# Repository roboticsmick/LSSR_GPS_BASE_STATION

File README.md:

# LSSR_GPS_BASE_STATION

A portable, low cost GPS Rocket tracking base station. Uses a Teensy 4.1 and Ebytes LORA module to track and display the current GPS coordinates for a HPR rocket launch. Estimated range is 7km.

This was designed and built for my HPR L1 certification launch. Tracking worked perfectly and I was able to successfully monitor the launch of my rocket, then use the GPS coordinates to locate it’s landing point.

Parts list:
* Microcontroller – TEENSY 4.1
* RF receiver – EbyteLORA E22-900T22D (set to 915Mhz for Australia)
* GPS – UBLOX NEO_6M (also works with ATGM336H GPS Module)
* 5V Buck Converter – MPM3610 5V at 1.2A
* Compass – GY271 QMC5883 LCD – OLED 128×64
* Battery – 7.4V LIPO with XT30 connection

Version 2 will use a Raspberry Pi Pico RP2040 to bring the overall costs of the board down.

PCB design was done using Fusion 360 electronics. 

PCB printed using JLCPCB.

Case design is lasercut perspex and 3D printed. Modelled using Fusion 360.

Instructions:
When recording GPS coodinates for launch data. 
1. Power using a USB only (do not turn on the toggle switch).
2. Connect to PC using USB. 
3. Use the device manager to identify which COM port the GPS Base Station is connected to.

4. Open putty (don't use the serial monitor in Arduino as it does not allow saving data and has a limited number of rows).
5. Set to serial and change the COM port to match the ID found in the device manager.

6. Base stations should automaticaly pick up the GPS tracker when turned on.
7. The base station will start displaying GPS coordinates on the LCD when it has a fix.
8. SIV = Satellites in view. At least 3 should be in view to get valid data. 
9. When the rocket has landed, save the GPS coordinate data from putty as a CSV. 
10. Copy the last row of the saved data and paste it into Googlemaps. The rocket coordinates should now be available.

If the rocket coordinates were lost:
1. Unplug the USB, and turn on the GPS base station using the toggle switch.
2. Head in the direction of the last known coordinates.
3. When new coordinates are recieved by the base station, the GPS base station should update on the LCD when the rocket is detected. 
4. If you cannot see the rocket, enter the updated coordinates into your phones googlemaps, and you should be able to work out the location in the field.

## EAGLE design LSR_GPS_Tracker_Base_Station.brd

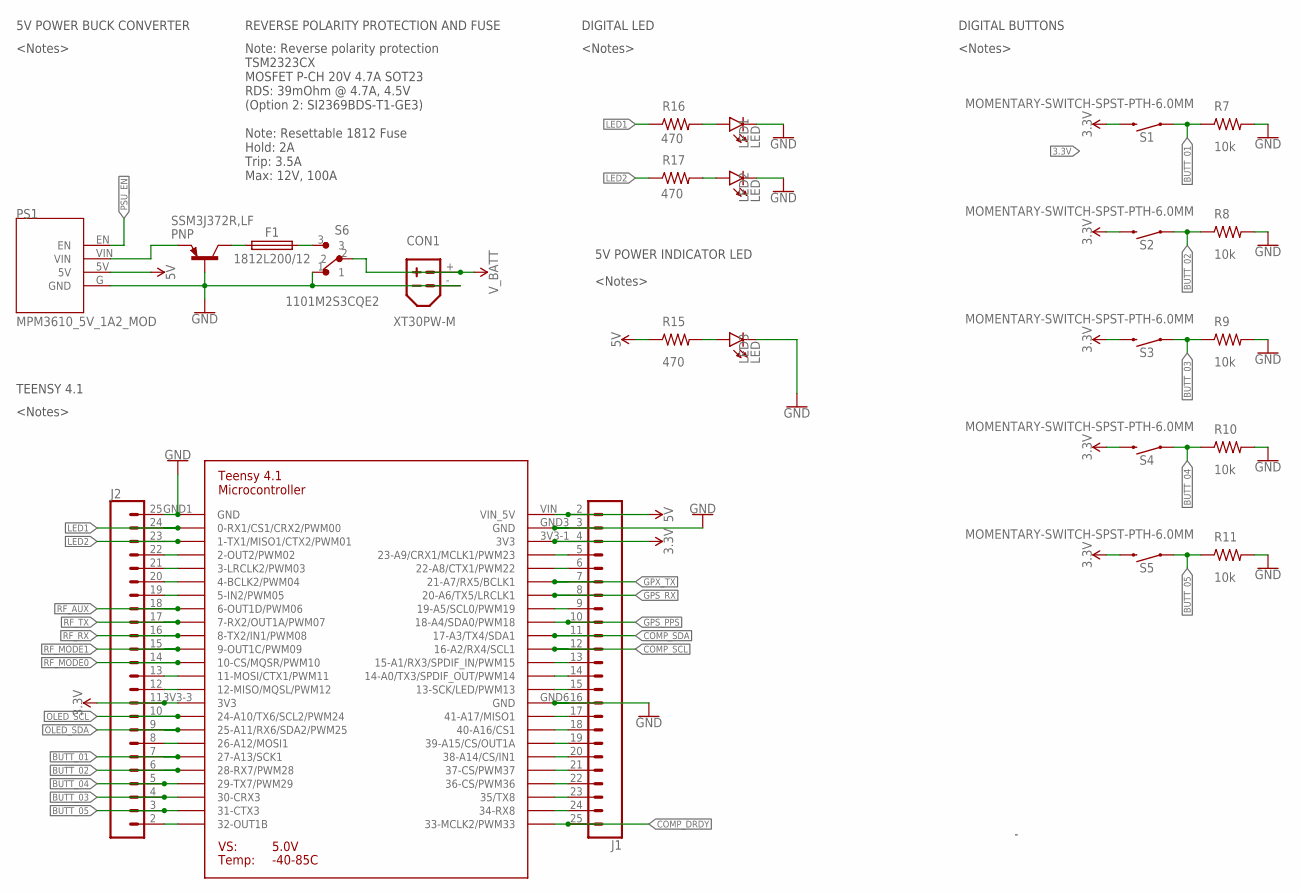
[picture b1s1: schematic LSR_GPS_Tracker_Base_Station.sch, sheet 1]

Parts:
CON1: XT30PW-M; XT30PW-PLUG
F1: 1812L200/12; FUSC4532X125
J1, J2: CONN_24; 1X24
LED1, LED2, LED3: LED; 0805_LED
PS1: MPM3610_5V_1A2_MOD; MPM3610_5V_1A2_FP
R7, R8, R9, R10, R11: 10k; 0805_RESISTOR_FP
R15, R16, R17: 470; 0805_RESISTOR_FP
S1, S2, S3, S4, S5: MOMENTARY-SWITCH-SPST-PTH-6.0MM; TACTILE_SWITCH_PTH_6.0MM
S6: 1101M2S3CQE2; SW_1101M2S3CQE2
SSM3J372R,LF: PNP; SOT95P237X112-3N
U$3: TEENSY_4_1; TEENSY_4_1_FP

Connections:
3.3V: J1.4, J2.11, S1.3 (2), S2.3 (2), S3.3 (2), S4.3 (2), S5.3 (2), U$3.3V3-1 (3V3), U$3.3V3-3 (3V3); also elsewhere on the board
5V: J1.2, PS1.5V, R15.1, U$3.VIN (VIN_5V); also elsewhere on the board
BUTT_01: J2.7, R7.1, S1.1, U$3.27-A13/SCK1
BUTT_02: J2.6, R8.1, S2.1, U$3.28-RX7/PWM28
BUTT_03: J2.4, R9.1, S3.1, U$3.30-CRX3
BUTT_04: J2.5, R10.1, S4.1, U$3.29-TX7/PWM29
BUTT_05: J2.3, R11.1, S5.1, U$3.31-CTX3
COMP_DRDY: J1.25, U$3.33-MCLK2/PWM33; also elsewhere on the board
COMP_SCL: J1.12, U$3.16-A2/RX4/SCL1; also elsewhere on the board
COMP_SDA: J1.11, U$3.17-A3/TX4/SDA1; also elsewhere on the board
GND: CON1.-, J1.3, J1.16, J2.25, LED1.C, LED2.C, LED3.C, PS1.G (GND), R7.2, R8.2, R9.2, R10.2, R11.2, S6.1, SSM3J372R,LF.1 (B), U$3.GND1 (GND), U$3.GND3 (GND), U$3.GND6 (GND); also elsewhere on the board
GPS_PPS: J1.10, U$3.18-A4/SDA0/PWM18; also elsewhere on the board
GPS_RX: J1.8, U$3.20-A6/TX5/LRCLK1; also elsewhere on the board
GPX_TX: J1.7, U$3.21-A7/RX5/BCLK1; also elsewhere on the board
LED1: J2.24, R16.1, U$3.0-RX1/CS1/CRX2/PWM00
LED2: J2.23, R17.1, U$3.1-TX1/MISO1/CTX2/PW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
unnamed: J1.5, U$3.23-A9/CRX1/MCLK1/PW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
unnamed: J1.6, U$3.22-A8/CTX1/PWM22
unnamed: J1.13, U$3.15-A1/RX3/SPDIF_IN/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
unnamed: J2.2, U$3.32-OUT1B
unnamed: J1.14, U$3.14-A0/TX3/SPDIF_OUT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
unnamed: J1.15, U$3.13-SCK/LED/PWM13
unnamed: J1.17, U$3.41-A17/MISO1
unnamed: J1.18, U$3.40-A16/CS1
unnamed: J1.19, U$3.39-A15/CS/OUT1A
unnamed: J1.20, U$3.38-A14/CS/IN1
unnamed: J1.21, U$3.37-CS/PWM37
unnamed: J1.22, U$3.36-CS/PWM36
unnamed: J1.23, U$3.35-TX8 (35/TX8)
unnamed: J1.24, U$3.34-RX8
unnamed: J1.9, U$3.19-A5/SCL0/PWM19
unnamed: J2.21, U$3.3-LRCLK2/PWM03
unnamed: J2.20, U$3.4-BCLK2/PWM04
unnamed: J2.19, U$3.5-IN2/PWM05
unnamed: J2.13, U$3.11-MOSI/CTX1/PWM11
unnamed: J2.12, U$3.12-MISO/MQSL/PWM12
unnamed: J2.8, U$3.26-A12/MOSI1
unnamed: J2.22, U$3.2-OUT2/PWM02
unnamed: LED3.A, R15.2
unnamed: LED1.A, R16.2
unnamed: F1.2, S6.3
unnamed: F1.1, SSM3J372R,LF.3 (C)
unnamed: PS1.VIN, SSM3J372R,LF.2 (E)
unnamed: LED2.A, R17.2
OLED_SCL: J2.10, U$3.24-A10/TX6/SCL2/PWM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; also elsewhere on the board
OLED_SDA: J2.9, U$3.25-A11/RX6/SDA2/PWM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; also elsewhere on the board
PSU_EN: PS1.EN
RF_AUX: J2.18, U$3.6-OUT1D/PWM06; also elsewhere on the board
RF_MODE0: J2.14, U$3.10-CS\MQSR/PWM10 (10-CS/MQSR/PWM10); also elsewhere on the board
RF_MODE1: J2.15, U$3.9-OUT1C/PWM09; also elsewhere on the board
RF_RX: J2.16, U$3.8-TX2/IN1/PWM08; also elsewhere on the board
RF_TX: J2.17, U$3.7-RX2/OUT1A/PWM07; also elsewhere on the board
V_BATT: CON1.+, S6.2

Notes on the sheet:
DIGITAL BUTTONS
5V POWER BUCK CONVERTER
DIGITAL LED
5V POWER INDICATOR LED
REVERSE POLARITY PROTECTION AND FUSE
TEENSY 4.1
<Notes>
Note: Reverse polarity protection TSM2323CX MOSFET P-CH 20V 4.7A SOT23 RDS: 39mOhm @ 4.7A, 4.5V (Option 2: SI2369BDS-T1-GE3) Note: Resettable 1812 Fuse Hold: 2A Trip: 3.5A Max: 12V, 100A

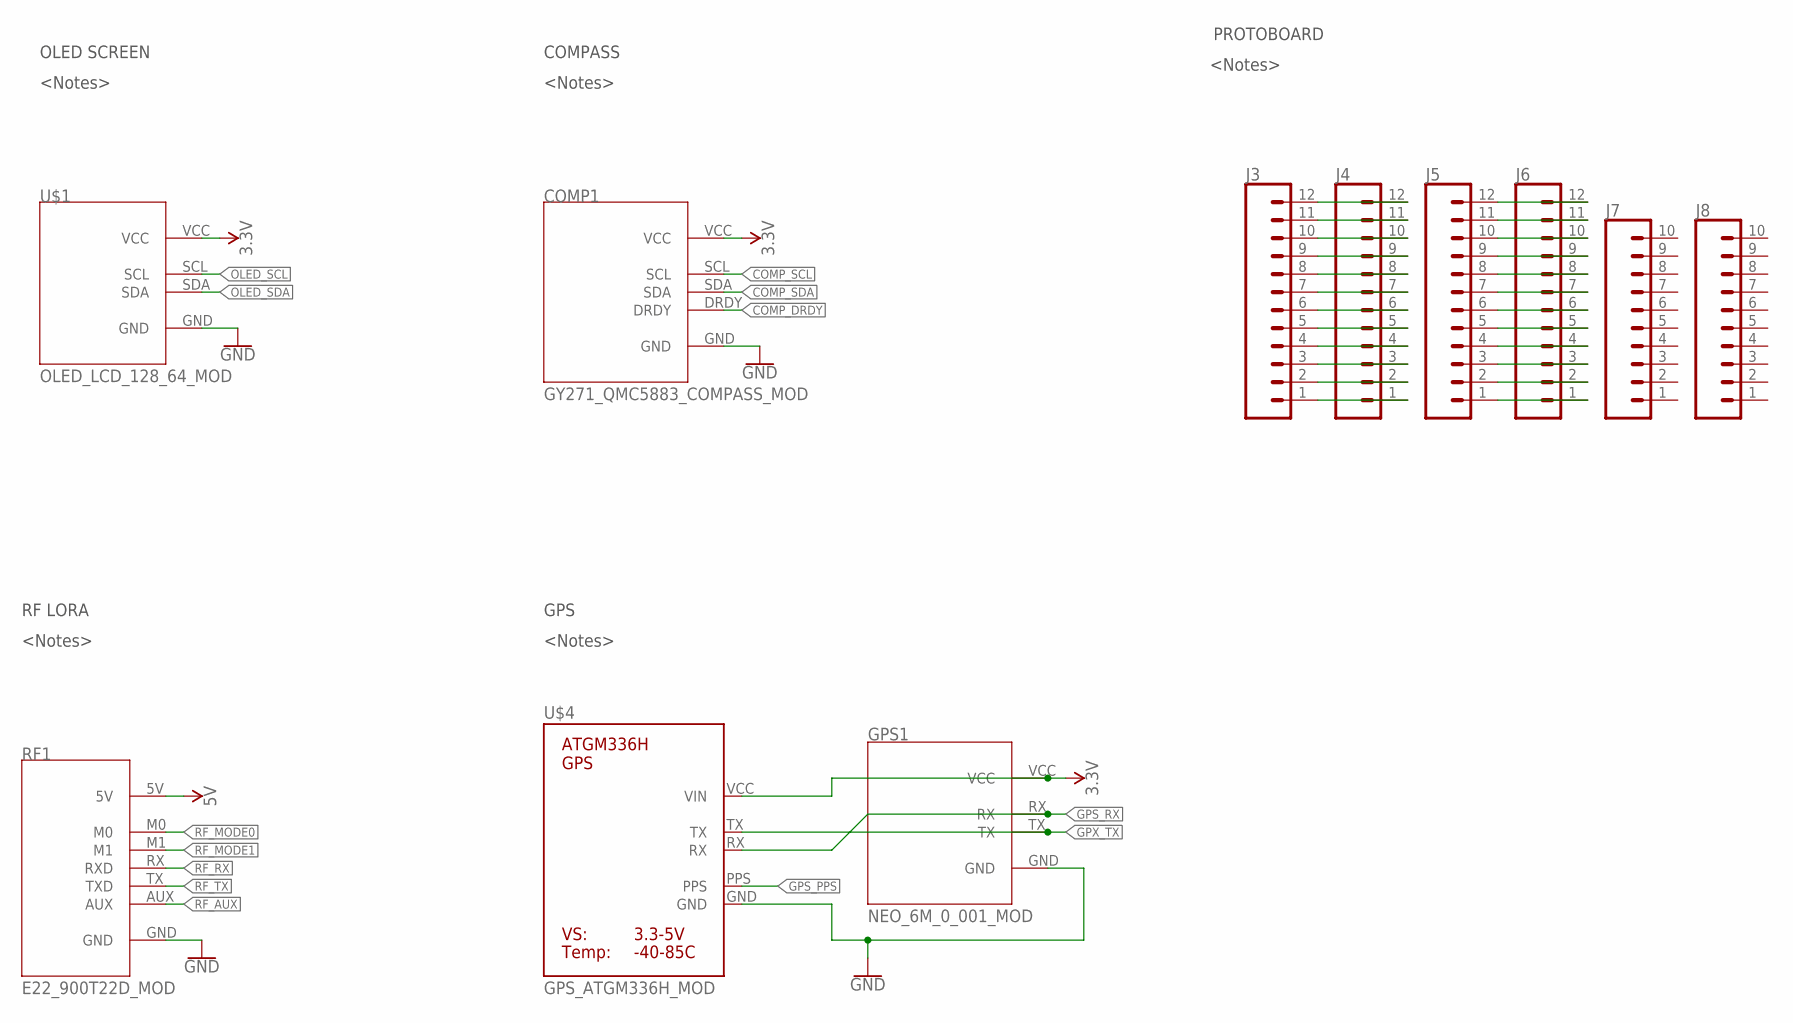
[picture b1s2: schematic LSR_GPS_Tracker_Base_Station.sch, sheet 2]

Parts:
COMP1: GY271_QMC5883_COMPASS_MOD; GY271_QMC5883_COMPASS_MOD_FP
GPS1: NEO_6M_0_001_MOD; NEO_6M_0_001_MOD_FP
J3, J4, J5, J6: CONN_12NO_SILK; 1X12_NO_SILK
J7, J8: CONN_10NO_SILK_PTH_FEMALE; 1X10_NO_SILK
RF1: E22_900T22D_MOD; E22_900T22D_MOD_FP
U$1: OLED_LCD_128_64_MOD; OLED_LCD_128_64_MOD_FP
U$4: GPS_ATGM336H_MOD; GPS_ATGM336H_FP

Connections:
3.3V: COMP1.VCC, GPS1.VCC, U$1.VCC, U$4.VCC (VIN); also elsewhere on the board
5V: RF1.5V; also elsewhere on the board
COMP_DRDY: COMP1.DRDY; also elsewhere on the board
COMP_SCL: COMP1.SCL; also elsewhere on the board
COMP_SDA: COMP1.SDA; also elsewhere on the board
GND: COMP1.GND, GPS1.GND, RF1.GND, U$1.GND, U$4.GND; also elsewhere on the board
GPS_PPS: U$4.PPS; also elsewhere on the board
GPS_RX: GPS1.RX, U$4.RX; also elsewhere on the board
GPX_TX: GPS1.TX, U$4.TX; also elsewhere on the board
unnamed: J3.12, J4.12
unnamed: J3.11, J4.11
unnamed: J3.10, J4.10
unnamed: J3.9, J4.9
unnamed: J3.8, J4.8
unnamed: J3.7, J4.7
unnamed: J3.6, J4.6
unnamed: J3.5, J4.5
unnamed: J3.4, J4.4
unnamed: J3.3, J4.3
unnamed: J3.2, J4.2
unnamed: J3.1, J4.1
unnamed: J5.12, J6.12
unnamed: J5.11, J6.11
unnamed: J5.10, J6.10
unnamed: J5.9, J6.9
unnamed: J5.8, J6.8
unnamed: J5.7, J6.7
unnamed: J5.6, J6.6
unnamed: J5.5, J6.5
unnamed: J5.4, J6.4
unnamed: J5.3, J6.3
unnamed: J5.2, J6.2
unnamed: J5.1, J6.1
OLED_SCL: U$1.SCL; also elsewhere on the board
OLED_SDA: U$1.SDA; also elsewhere on the board
RF_AUX: RF1.AUX; also elsewhere on the board
RF_MODE0: RF1.M0; also elsewhere on the board
RF_MODE1: RF1.M1; also elsewhere on the board
RF_RX: RF1.RX (RXD); also elsewhere on the board
RF_TX: RF1.TX (TXD); also elsewhere on the board

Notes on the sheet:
PROTOBOARD
GPS
RF LORA
COMPASS
OLED SCREEN
<Notes>

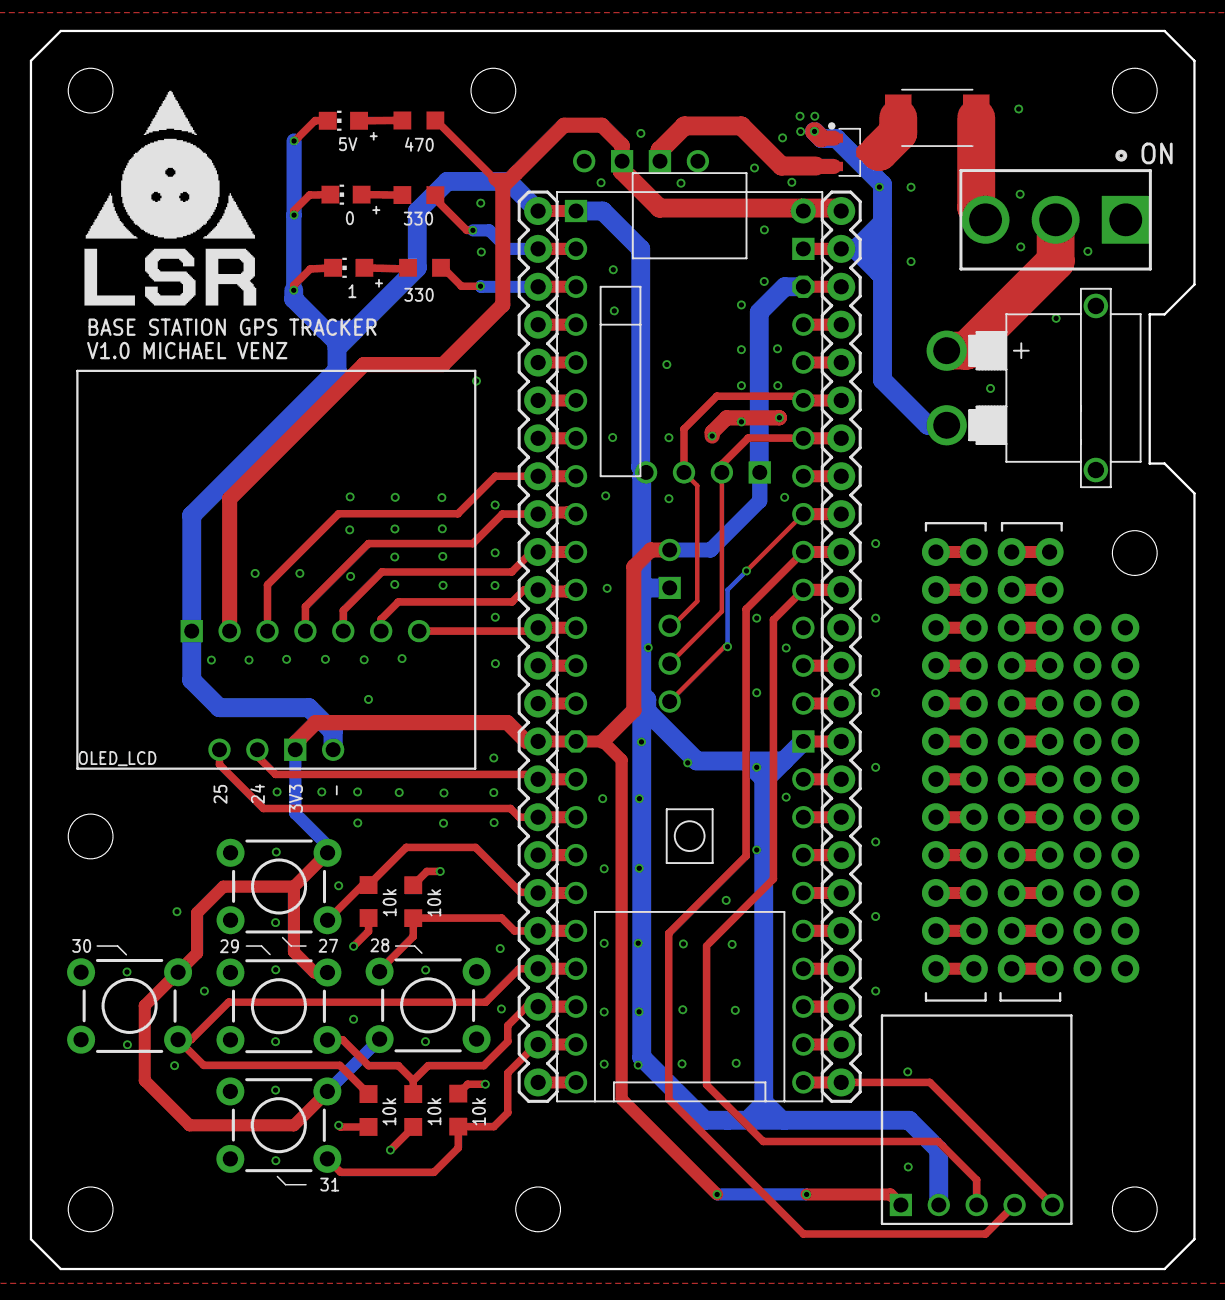
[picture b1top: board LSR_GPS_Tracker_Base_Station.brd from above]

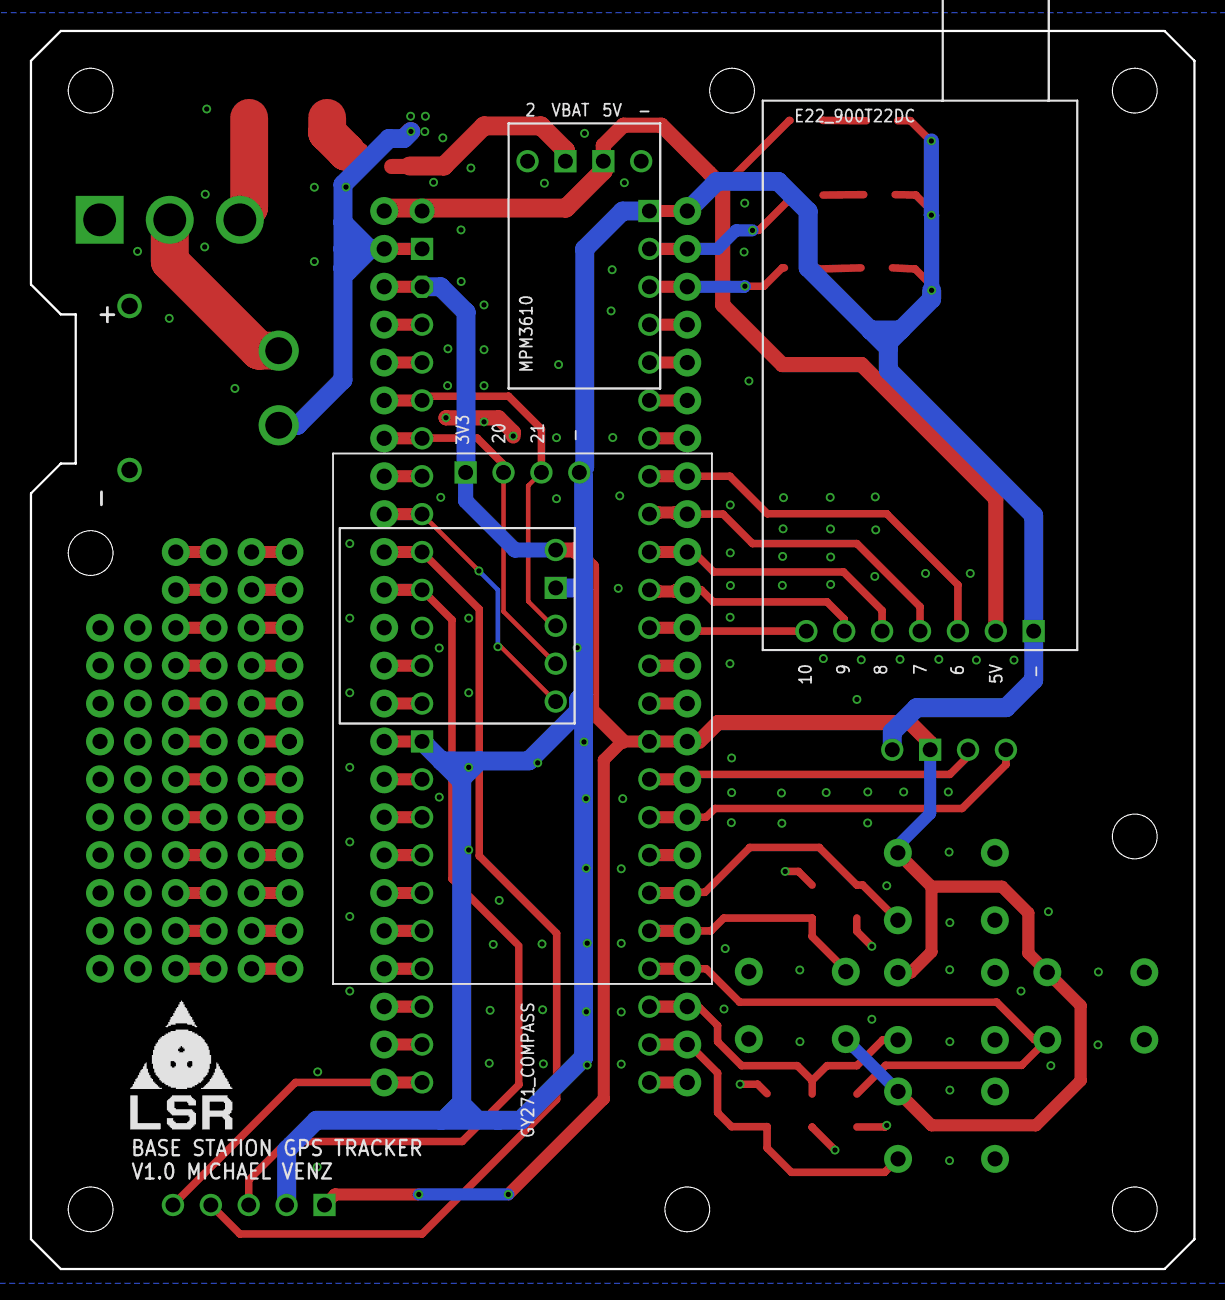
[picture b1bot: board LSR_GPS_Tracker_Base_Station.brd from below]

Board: 2 copper layers, 78.0 x 83.0 mm, 37 parts (5 on the bottom side), 76 nets.

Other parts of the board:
U$2: LSR_LOGO_TEXT_200PX_FP
U$5: LSR_LOGO_TEXT_120PX_FP

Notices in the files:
parts and their libraries:
SparkFun-Connectors: Licensing: Creative Commons ShareAlike 4.0 International - https://creativecommons.org/licenses/by-sa/4.0
